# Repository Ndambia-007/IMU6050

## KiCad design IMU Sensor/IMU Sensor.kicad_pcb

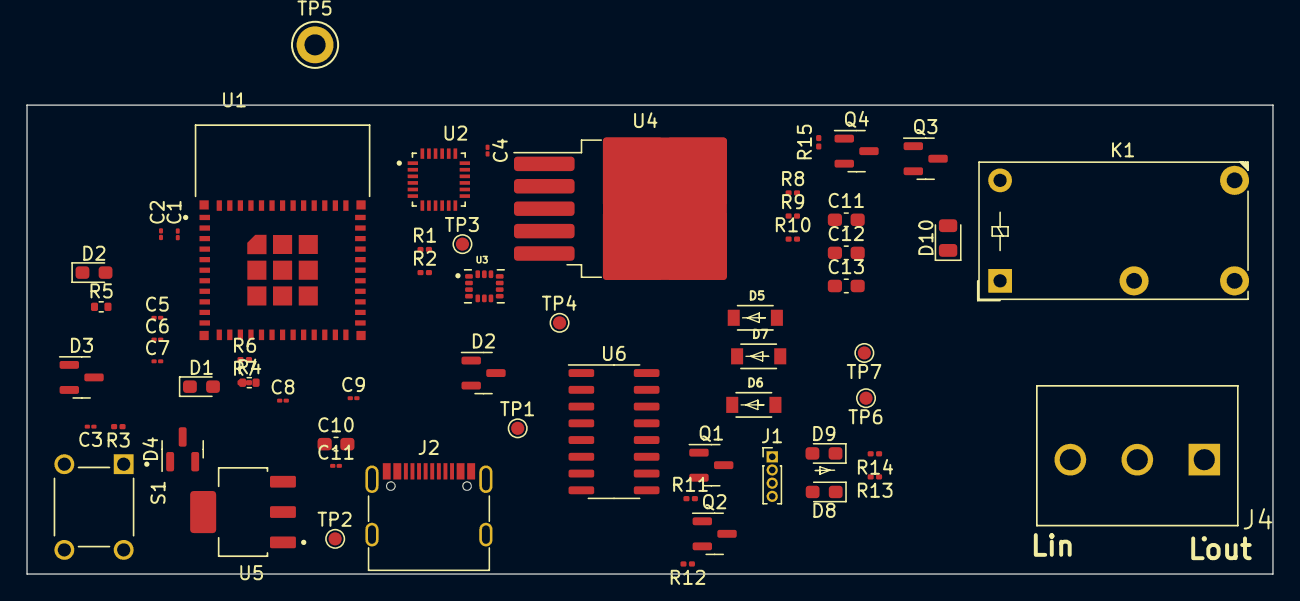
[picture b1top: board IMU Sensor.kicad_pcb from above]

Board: 2 copper layers, 94.5 x 35.6 mm, 62 parts (0 on the bottom side), 38 nets, no tracks yet.

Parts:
C1: 10uF; C_01005_0402Metric
C2, C3, C5, C6, C8, C9: 0.1uF; C_01005_0402Metric
C4: 2.2nF; C_01005_0402Metric
C7: 10nF; C_01005_0402Metric
C10, C12: 10uF; C_0603_1608Metric_Pad1.08x0.95mm_HandSolder
C11: 100uF; C_01005_0402Metric
C11#2: 1000uF; C_0603_1608Metric_Pad1.08x0.95mm_HandSolder
C13: 0.1uF; C_0603_1608Metric_Pad1.08x0.95mm_HandSolder
D1: Red Led; LED_0603_1608Metric_Pad1.05x0.95mm_HandSolder
D2: Status Led; LED_0603_1608Metric_Pad1.05x0.95mm_HandSolder
D2#2, D3, D4: SP0502BAHT; SOT-23
D5, D6, D7: D_Schottky; DIO_MMSZ4700T1G
D8: TX; LED_0603_1608Metric_Pad1.05x0.95mm_HandSolder
D9: RX; LED_0603_1608Metric_Pad1.05x0.95mm_HandSolder
D10: CD4148W; D_0805_2012Metric
J1: Conn_01x04_Pin; PinHeader_1x04_P1.00mm_Vertical
J2: USB_C_Receptacle_USB2.0; USB_C_Receptacle_G-Switch_GT-USB-7010ASV
J4: Screw_Terminal_01x03; CUI_TB009-508-03BE
K1: Relay_SPDT; Relay_SPDT_Finder_32.21-x000
Q1, Q2, Q3, Q4: BC847; SOT-23
R1, R2, R6, R7, R10: 4.7k; R_0201_0603Metric
R3, R9, R11, R12, R15: 10k; R_0201_0603Metric
R4, R5: 10k; R_0402_1005Metric
R8: 13.19k; R_0201_0603Metric
R13, R14: 1k; R_0201_0603Metric
S1: TS02-66-95-BK-260-LCR-D; SW_TS02-66-95-BK-260-LCR-D
TP1, TP2, TP6: TX; TestPoint_Pad_D1.0mm
TP3: SDA; TestPoint_Pad_D1.0mm
TP4: SCL; TestPoint_Pad_D1.0mm
TP5: GND; TestPoint_Keystone_5010-5014_Multipurpose
TP7: RX; TestPoint_Pad_D1.0mm
U1: ESP32-PICO-MINI-02; MODULE_ESP32-PICO-MINI-02
U2: MPU-6050; QFN50P400X400X95-24N
U3: ICM-42688-P; PQFN50P300X250X97-14N
U4: IFX25401TBV; TO-263-5_TabPin3
U5: ADP3338AKCZ-1.8-R7; SOT230P700X180-4N
U6: CH340C; SOIC-16_3.9x9.9mm_P1.27mm

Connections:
+3.3V: C1.1, C2.1, C6.1, C7.2, C8.1, C9.1, C11.1, C11#2.1, C13.1, D10.1 (K), J1.1, K1.A1, R1.1, R2.1, R3.1, R4.1, R8.1, TP2.1, U1.3 (3V3), U2.8 (VLOGIC), U2.13 (VDD), U3.5 (VDDIO), U3.8 (VDD), U4.5 (Q), U5.2 (OUT), U5.4 (OUT), U6.4 (V3), U6.16 (VCC)
+5V: C10.1, C12.1, J2.A4 (VBUS), J2.A9 (VBUS), J2.B4 (VBUS), J2.B9 (VBUS), R10.1, TP1.1, U4.1 (I), U5.3 (IN)
/IO_0: D5.2 (A), U1.23 (IO0)
/IO_2: D7.2 (A), U1.22 (IO2)
/RST: C3.1, D6.2 (A), R3.2, S1.1, S1.2, U1.8 (EN)
CS: U1.17 (IO27), U3.12 (AP_CS)
D+: D4.1 (K), J2.A6 (D+), J2.B6 (D+), U6.5 (UD+)
D-: D4.2 (K), J2.A7 (D-), J2.B7 (D-), U6.6 (UD-)
GND: C1.2, C2.2, C3.2, C4.2, C5.2, C6.2, C7.1, C8.2, C9.2, C10.2, C11.2, C11#2.2, C12.2, C13.2, D1.1 (K), D2.1 (K), D3.3 (A), D4.3 (A), J1.4, J2.A1 (GND), J2.A12 (GND), J2.B1 (GND), J2.B12 (GND), J2.S1 (SHIELD), Q3.2 (E), Q4.2 (E), R6.1, R7.1, R9.2, R13.1, R14.1, R15.1, S1.3, S1.4, TP5.1, U1.1 (GND), U1.2 (GND), U1.11 (GND), U1.14 (GND), U1.36 (GND), U1.37 (GND), U1.38 (GND), U1.39 (GND), U1.40 (GND), U1.41 (GND), U1.42 (GND), U1.43 (GND), U1.44 (GND), U1.45 (GND), U1.46 (GND), U1.47 (GND), U1.48 (GND), U1.49 (GND), U1.50 (GND), U1.51 (GND), U1.52 (GND), U1.53 (GND), U1.54 (GND), U1.55 (GND), U1.56 (GND), U1.57 (GND), U1.58 (GND), U1.59 (GND), U1.60 (GND), U1.61 (GND), U2.1 (CLKIN), U2.9 (AD0), U2.11 (FSYNC), U2.18 (GND), U3.6 (GND), U3.7 (RESV_7), U3.9 (INT2/FSYNC/CLKIN), U3.11 (RESV_11), U4.3 (GND), U5.1 (GND), U6.1 (GND)
INIT_ICM: U1.33 (IO19), U3.4 (INT1/INT)
INIT_MPU: U1.16 (IO26), U2.12 (INT)
LED: R5.1, U1.12 (IO32)
unnamed: D1.2 (A), R4.2
unnamed: D2.2 (A), R5.2
unnamed: D5.1 (K), D7.1 (K), Q2.3 (C)
unnamed: D6.1 (K), Q1.3 (C)
unnamed: D8.1 (K), R13.2
unnamed: D9.1 (K), R14.2
unnamed: D10.2 (A), K1.A2, Q3.3 (C)
unnamed: D3.2 (K), J2.A5 (CC1), R7.2
unnamed: D3.1 (K), J2.B5 (CC2), R6.2
unnamed: J4.1, K1.12
unnamed: J4.2, K1.14
unnamed: J4.3, K1.11
unnamed: Q1.1 (B), R12.2
unnamed: Q1.2 (E), R11.1, U6.13 (~DTR)
unnamed: Q2.1 (B), R11.2
unnamed: Q2.2 (E), R12.1, U6.14 (~RTS)
unnamed: Q3.1 (B), Q4.3 (C)
unnamed: C4.1, U2.20 (CPOUT)
unnamed: C5.1, U2.10 (REGOUT)
unnamed: R10.2, U4.2 (EN)
unnamed: R8.2, R9.1, U4.4 (VA)
RX: D9.2 (A), J1.2, TP7.1, U1.30 (RXD0), U6.3 (RXD)
Relay: Q4.1 (B), R15.2, U1.13 (IO33)
SCL: R1.2, TP4.1, U1.15 (IO25), U2.23 (SCL), U3.13 (AP_SCL/AP_SCLK)
SDA: R2.2, TP3.1, U1.34 (IO22), U2.24 (SDA), U3.14 (AP_SDA/AP_SDIO/AP_SDI)
TX: D8.2 (A), J1.3, TP6.1, U1.31 (TXD0), U6.2 (TXD)

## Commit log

2024-05-30 Add files via upload
    today's Progress
2024-05-31 Add files via upload
    Complete schematics
2024-06-03 Add files via upload
    Today progress is here
